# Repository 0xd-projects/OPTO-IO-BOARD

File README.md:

# OPTO-IO-BOARD

This board provides 16 independent voltage detection channels.  The channels can be configured to detect Open/Ground signals or Open/5-40V signals.  Each channel has a LED that indicates if the channel is ON or OFF, a currently limiting Resistor and an Opto-Isolator.  Each channel is then inputted into the MCP23017 IC that is setup as an Open/Ground detect.  The MCP23017 has an internal 100K internal pullup to 3.3V that is grounded by the Opto-Isolator when the Input is Active.  The MCP23017 samples it's inputs and reports their state over the I2C bus.  The Adafruit HUZZAH32 - ESP32 Feather board is used to poll the MCP23017 and send the current state of the channels over the network.  The HUZZAH32 Feather can be used over Wifi or with the optional Ethernet FeatherWing.

The board was designed to provide a large input voltage range.  The input circuit is a series of two diodes and any input that provides enough current to activate the diodes will trigger the input.  The input trigger point is approximately 33ua because the Opto-isolator only has to sink the 33ua provided by the MCP23017 100K pullup to 3.3V.  A input 0.5V over the two diodes forward voltage is enough to do this.  The minimum input of 5V is more than enough to trigger this as the LED ( approx 2.2V ) and opto-isolator ( approx 1.2V ) have a combined forward voltage of approximately 3.4V and the Opto-isolator has a gain of approximately 70% at this low current level so ( (5V - 3.4V) / 10K ) * 70% => 112ua which is more than the 33ua sourced by the pullup resistor.  Note: Some LEDs can have a forward voltage as high as 3.3V which would result in a current of 35ua just a little bit more than the 33ua required.

If you would like to change the voltage level trigger you can add a Zener diode in series to the input circuit.  The Zener diode will increase the input level trigger by it's value + approximately 5V.  So, if you want to trigger at say 20V you can put a 15V Zener diode in series on the input.

The input voltage is limited by 10K resistor at 1/2W and the max steady state current rating of the input diodes ( Typically 20ma ).  At 40V input there is only approximately 3.66ma of current at 0.133W going through the input circuit this is far below the LED's 20ma max at around 4W.  The input was rated at 40V ( approximately 27% load ) as a very conservative limit not knowing what conditions the circuit would be used in.  The real 50% max input threshold is approximately 53.4V at around 1/4W and 5ma.  The 100% load is approximately 74V at around 1/2W and 7ma.

Folder structure
- doc                : Contains PDFs of the board design and the BOM.
- hw                 : Contains the Gerber and Kiacad design files for the PCB.
- sw/opto            : Contains example source code for using the board with the optional Ethernet FeatherWing.
- sw/opto_wifi       : Contains example source code for using the board with wifi.
- sw/sample_receiver : Contains example source code to receive and print the channel status on change.

You can find an overview of the Adafruit HUZZAH32 - ESP32 board at the link below.
- https://learn.adafruit.com/adafruit-huzzah32-esp32-feather/overview

You can find an overview of the Adafruit Ethernet FeatherWing at the link below.
- https://learn.adafruit.com/adafruit-wiz5500-wiznet-ethernet-featherwing/overview

You can find the MCP23017 data sheet at the link below.
- https://cdn-shop.adafruit.com/datasheets/mcp23017.pdf

To build the code you need to download the following SW :
- HUZZAH32: https://learn.adafruit.com/adafruit-huzzah32-esp32-feather/using-with-arduino-ide
- Ethernet FeatherWing: https://learn.adafruit.com/adafruit-wiz5500-wiznet-ethernet-featherwing/usage
- MCP23017: https://github.com/adafruit/Adafruit-MCP23017-Arduino-Library

To edit the PCB design you can download Kicad at the link below.
- https://www.kicad.org/

## License
The contents of the doc and hw folders are licensed under the [Creative Commons Attribution 3.0 license](http://creativecommons.org/licenses/by/3.0/us/deed.en_US).
The contents of the sw folder is licensed under the [MIT license](http://opensource.org/licenses/mit-license.php).

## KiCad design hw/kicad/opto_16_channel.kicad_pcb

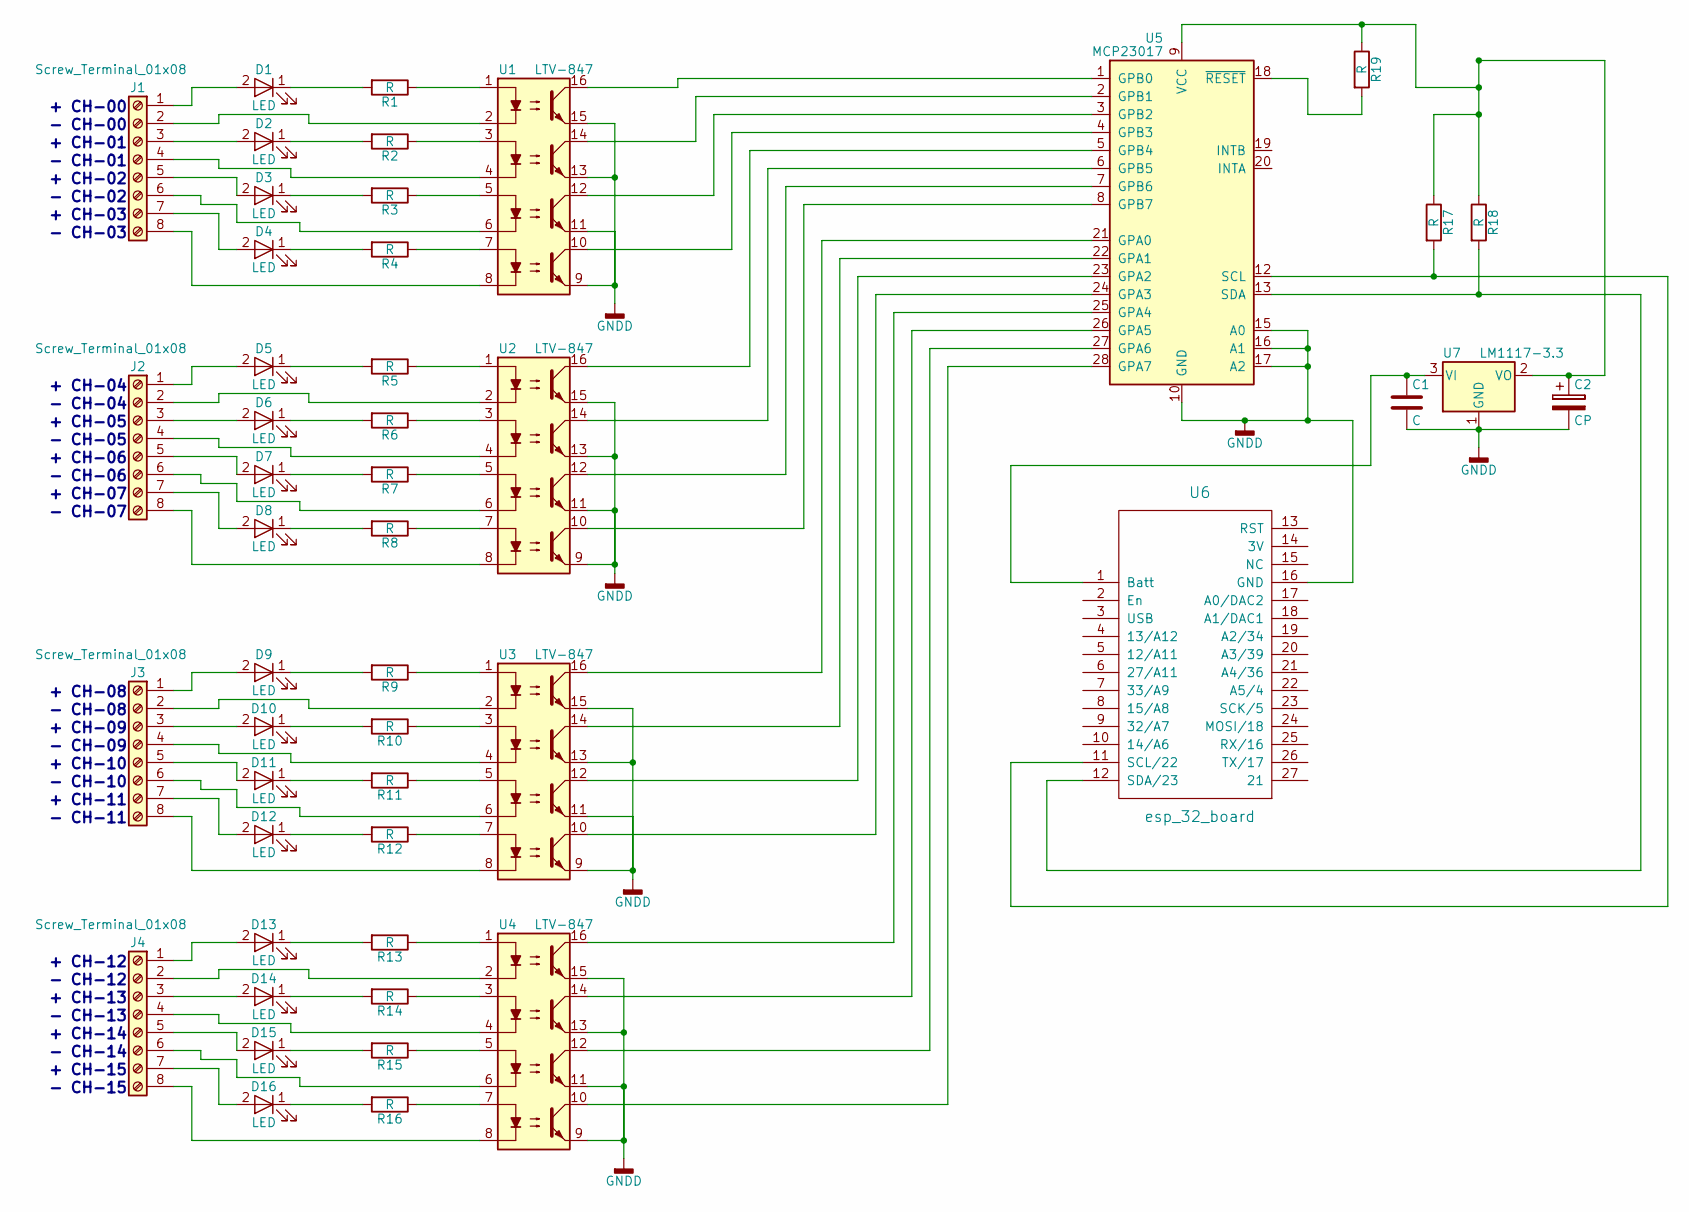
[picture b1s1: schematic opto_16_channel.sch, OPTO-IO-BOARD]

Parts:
C1: C; C_Disc_D4.3mm_W1.9mm_P5.00mm
C2: CP; CP_Radial_D5.0mm_P2.50mm
D1, D2, D3, D4, D5, D6, D7, D8, D9, D10, D11, D12, D13, D14, D15, D16: LED; LED_SideEmitter_Rectangular_W4.5mm_H1.6mm
J1, J2, J3, J4: Screw_Terminal_01x08; TerminalBlock_Pheonix_MPT-2.54mm_8pol
R1, R2, R3, R4, R5, R6, R7, R8, R9, R10, R11, R12, R13, R14, R15, R16, R17, R18, R19: R; R_Axial_DIN0207_L6.3mm_D2.5mm_P10.16mm_Horizontal
U1, U2, U3, U4: LTV-847; DIP-16_W7.62mm
U5: MCP23017; DIP-28_W7.62mm
U6: esp_32_board; ADAFRUIT_FEATHER
U7: LM1117-3.3; TO-220_Vertical

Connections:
GNDD: C1.2, C2.2, U1.9, U1.11, U1.13, U1.15, U2.9, U2.11, U2.13, U2.15, U3.9, U3.11, U3.13, U3.15, U4.9, U4.11, U4.13, U4.15, U5.10 (GND), U5.15 (A0), U5.16 (A1), U5.17 (A2), U6.16 (GND), U7.1 (GND)
unnamed: C1.1, U6.1 (Batt), U7.3 (VI)
unnamed: C2.1, R17.1, R18.1, R19.1, U5.9 (VCC), U7.2 (VO)
unnamed: D1.1 (K), R1.2
unnamed: D1.2 (A), J1.1
unnamed: D2.1 (K), R2.2
unnamed: D2.2 (A), J1.3
unnamed: D3.1 (K), R3.2
unnamed: D3.2 (A), J1.5
unnamed: D4.1 (K), R4.2
unnamed: D4.2 (A), J1.7
unnamed: D5.1 (K), R5.2
unnamed: D5.2 (A), J2.1
unnamed: D6.1 (K), R6.2
unnamed: D6.2 (A), J2.3
unnamed: D7.1 (K), R7.2
unnamed: D7.2 (A), J2.5
unnamed: D8.1 (K), R8.2
unnamed: D8.2 (A), J2.7
unnamed: D9.1 (K), R9.2
unnamed: D9.2 (A), J3.1
unnamed: D10.1 (K), R10.2
unnamed: D10.2 (A), J3.3
unnamed: D11.1 (K), R11.2
unnamed: D11.2 (A), J3.5
unnamed: D12.1 (K), R12.2
unnamed: D12.2 (A), J3.7
unnamed: D13.1 (K), R13.2
unnamed: D13.2 (A), J4.1
unnamed: D14.1 (K), R14.2
unnamed: D14.2 (A), J4.3
unnamed: D15.1 (K), R15.2
unnamed: D15.2 (A), J4.5
unnamed: D16.1 (K), R16.2
unnamed: D16.2 (A), J4.7
unnamed: J1.2, U1.2
unnamed: J1.4, U1.4
unnamed: J1.6, U1.6
unnamed: J1.8, U1.8
unnamed: J2.2, U2.2
unnamed: J2.4, U2.4
unnamed: J2.6, U2.6
unnamed: J2.8, U2.8
unnamed: J3.2, U3.2
unnamed: J3.4, U3.4
unnamed: J3.6, U3.6
unnamed: J3.8, U3.8
unnamed: J4.2, U4.2
unnamed: J4.4, U4.4
unnamed: J4.6, U4.6
unnamed: J4.8, U4.8
unnamed: R1.1, U1.1
unnamed: R2.1, U1.3
unnamed: R3.1, U1.5
unnamed: R4.1, U1.7
unnamed: R5.1, U2.1
unnamed: R6.1, U2.3
unnamed: R7.1, U2.5
unnamed: R8.1, U2.7
unnamed: R9.1, U3.1
unnamed: R10.1, U3.3
unnamed: R11.1, U3.5
unnamed: R12.1, U3.7
unnamed: R13.1, U4.1
unnamed: R14.1, U4.3
unnamed: R15.1, U4.5
unnamed: R16.1, U4.7
unnamed: R17.2, U5.12 (SCL), U6.11 (SCL/22)
unnamed: R18.2, U5.13 (SDA), U6.12 (SDA/23)
unnamed: R19.2, U5.18 (~RESET)
unnamed: U1.10, U5.4 (GPB3)
unnamed: U1.12, U5.3 (GPB2)
unnamed: U1.14, U5.2 (GPB1)
unnamed: U1.16, U5.1 (GPB0)
unnamed: U2.10, U5.8 (GPB7)
unnamed: U2.12, U5.7 (GPB6)
unnamed: U2.14, U5.6 (GPB5)
unnamed: U2.16, U5.5 (GPB4)
unnamed: U3.10, U5.24 (GPA3)
unnamed: U3.12, U5.23 (GPA2)
unnamed: U3.14, U5.22 (GPA1)
unnamed: U3.16, U5.21 (GPA0)
unnamed: U4.10, U5.28 (GPA7)
unnamed: U4.12, U5.27 (GPA6)
unnamed: U4.14, U5.26 (GPA5)
unnamed: U4.16, U5.25 (GPA4)

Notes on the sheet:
+ CH-00
- CH-00
+ CH-01
- CH-01
+ CH-02
- CH-02
+ CH-03
- CH-03
+ CH-04
- CH-04
+ CH-05
- CH-05
+ CH-06
- CH-06
+ CH-07
- CH-07
+ CH-08
- CH-08
+ CH-09
- CH-09
+ CH-10
- CH-10
+ CH-11
- CH-11
+ CH-12
- CH-12
+ CH-13
- CH-13
+ CH-14
- CH-14
+ CH-15
- CH-15

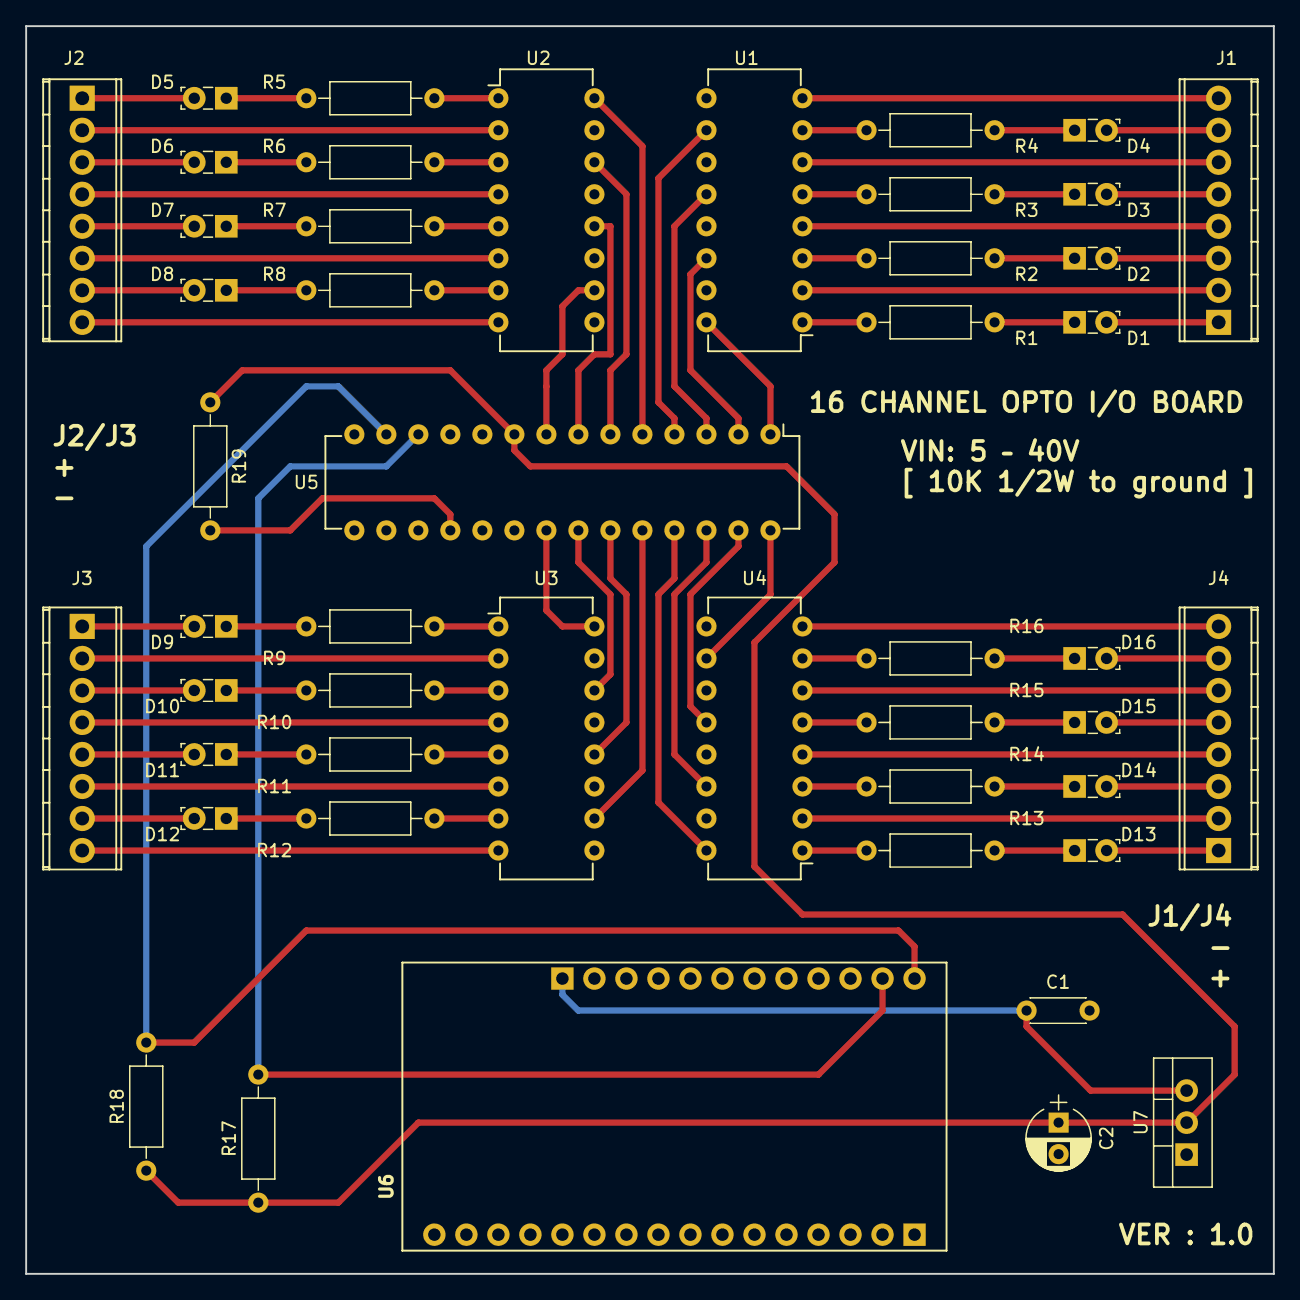
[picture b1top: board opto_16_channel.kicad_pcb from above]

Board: 2 copper layers, 99.0 x 99.0 mm, 48 parts (0 on the bottom side), 86 nets.

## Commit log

2017-11-13 initial check-in
2017-11-13 deleted file
2017-11-13 removed file
2017-11-13 updated ignore list
2017-11-14 Initial Doc and updates
2017-11-14 added example receive code.
2018-07-28 Added Wifi, Updated Ethernet
    Added wifi version, updated Ethernet version to 30hz update rate.
2018-07-29 Cleaned up readme
2018-08-04 Updated to 10K 1/2W resistor from 10K 2W resistor.
2022-04-16 Update README.md
    Fixed URL to kicad.
